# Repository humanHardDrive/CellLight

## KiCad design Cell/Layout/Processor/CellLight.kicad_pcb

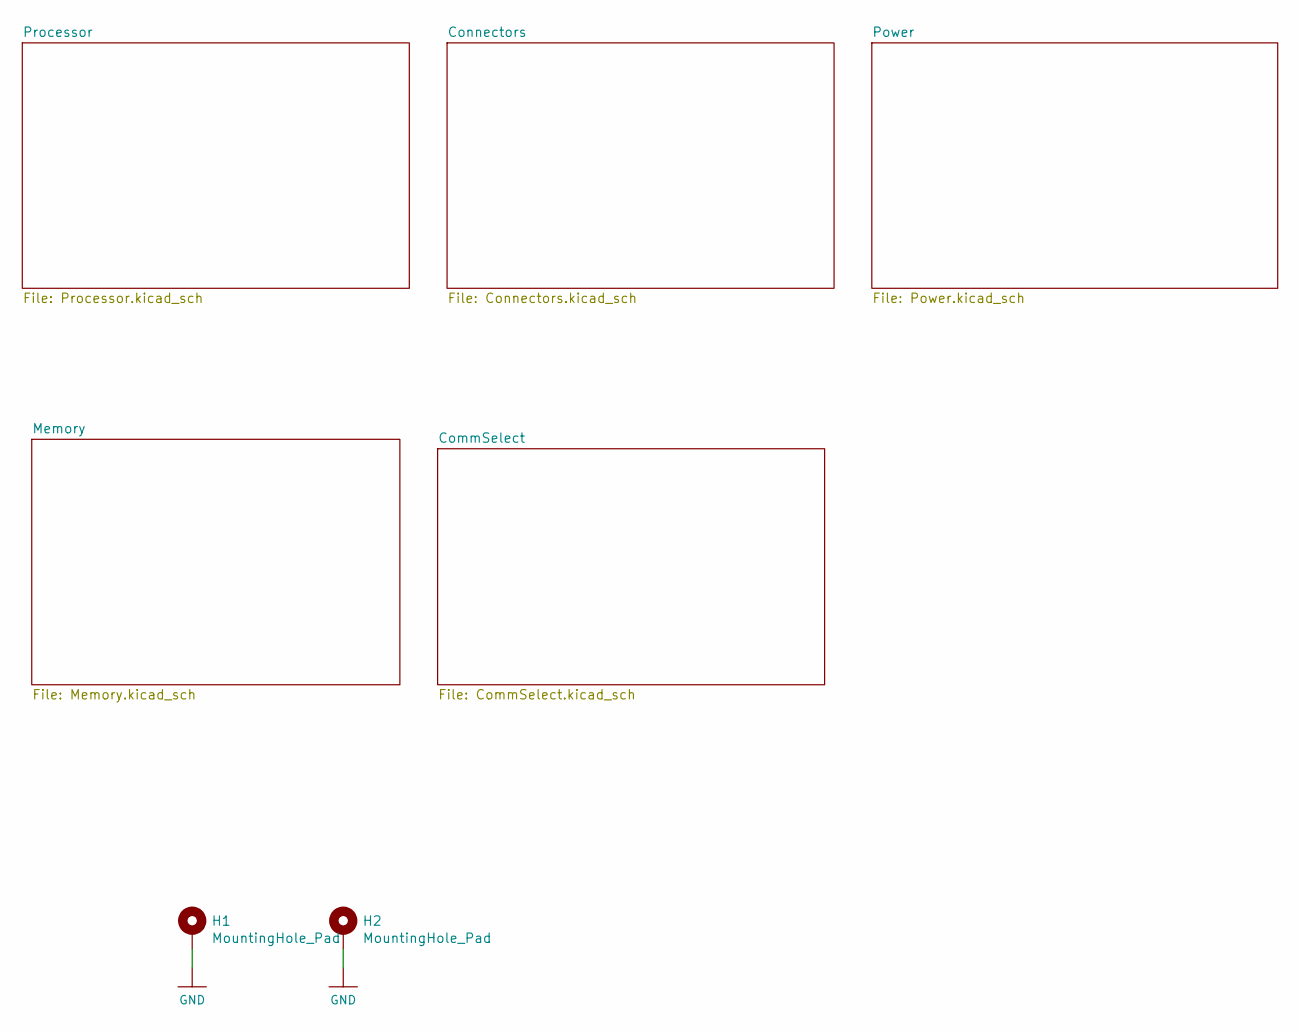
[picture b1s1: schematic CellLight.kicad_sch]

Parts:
H1, H2: MountingHole_Pad; MountingHole_2.7mm_M2.5_Pad

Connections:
GND: H1.1, H2.1; also elsewhere on the board

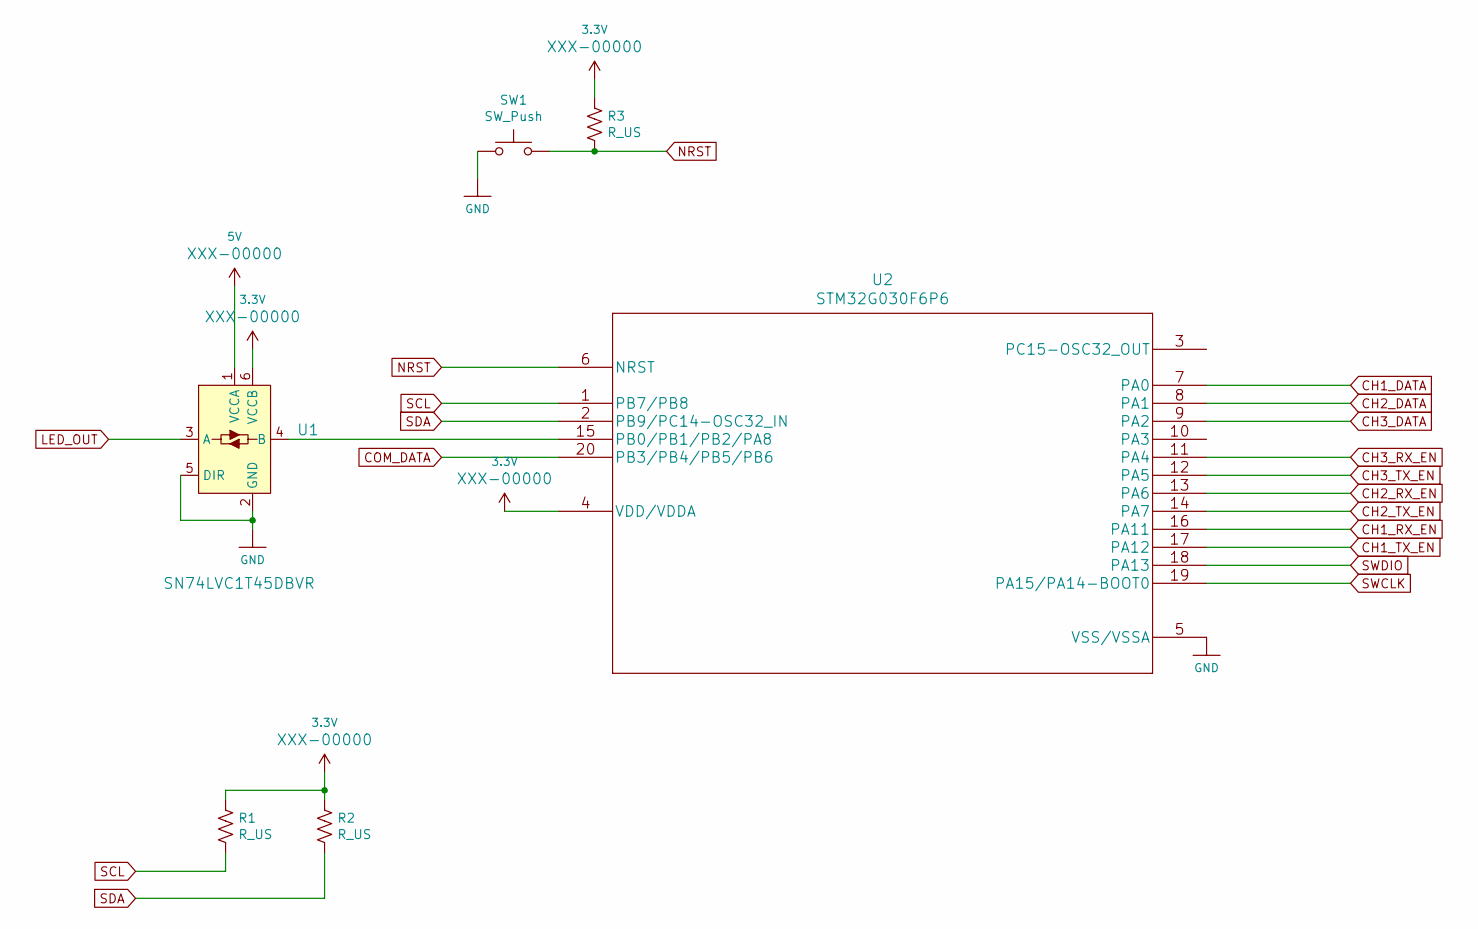
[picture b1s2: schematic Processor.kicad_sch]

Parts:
R1, R2, R3: R_US; R_0603_1608Metric_Pad1.05x0.95mm_HandSolder
SW1: SW_Push; SW_SPST_TL3342
U1: SN74LVC1T45DBVR; SOT-23-6; MPN SN74LVC1T45DBVR; Digi-Key_PN 296-16843-1-ND
U2: STM32G030F6P6

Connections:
3.3V: R1.1, R2.1, R3.1, U1.6 (VCCB), U2.4 (VDD/VDDA); also elsewhere on the board
5V: U1.1 (VCCA); also elsewhere on the board
CH1_DATA: U2.7 (PA0); also elsewhere on the board
CH1_RX_EN: U2.16 (PA11); also elsewhere on the board
CH1_TX_EN: U2.17 (PA12); also elsewhere on the board
CH2_DATA: U2.8 (PA1); also elsewhere on the board
CH2_RX_EN: U2.13 (PA6); also elsewhere on the board
CH2_TX_EN: U2.14 (PA7); also elsewhere on the board
CH3_DATA: U2.9 (PA2); also elsewhere on the board
CH3_RX_EN: U2.11 (PA4); also elsewhere on the board
CH3_TX_EN: U2.12 (PA5); also elsewhere on the board
COM_DATA: U2.20 (PB3/PB4/PB5/PB6); also elsewhere on the board
GND: SW1.1, U1.2 (GND), U1.5 (DIR), U2.5 (VSS/VSSA); also elsewhere on the board
LED_OUT: U1.3 (A); also elsewhere on the board
NRST: R3.2, SW1.2, U2.6 (NRST); also elsewhere on the board
unnamed: U1.4 (B), U2.15 (PB0/PB1/PB2/PA8)
SCL: R1.2, U2.1 (PB7/PB8); also elsewhere on the board
SDA: R2.2, U2.2 (PB9/PC14-OSC32_IN); also elsewhere on the board
SWCLK: U2.19 (PA15/PA14-BOOT0); also elsewhere on the board
SWDIO: U2.18 (PA13); also elsewhere on the board

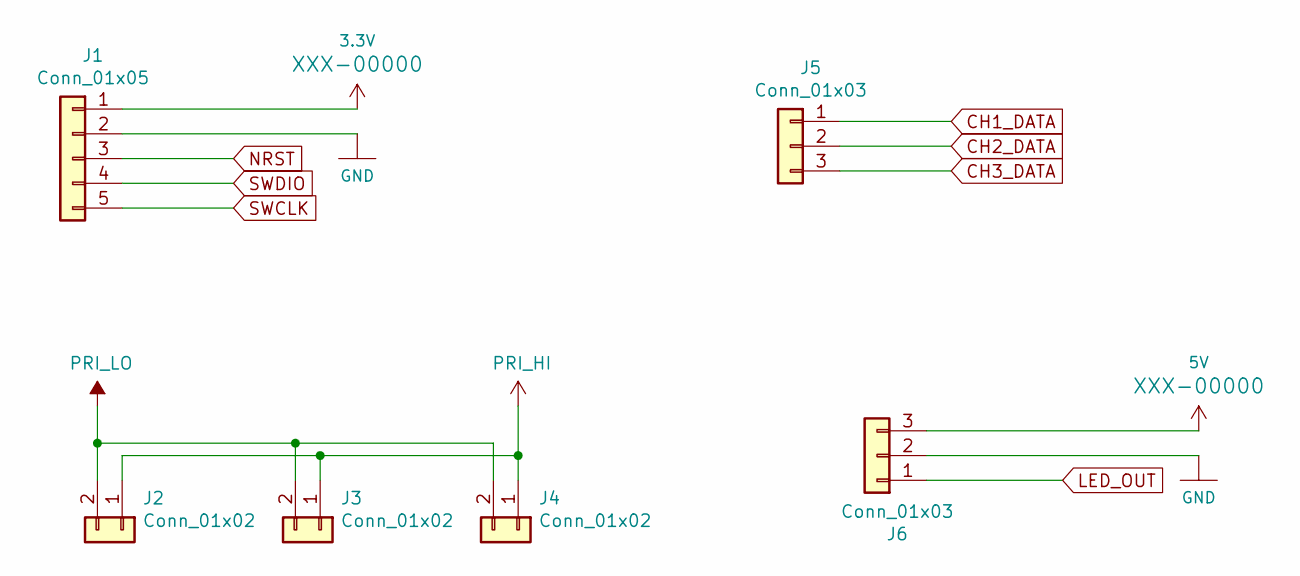
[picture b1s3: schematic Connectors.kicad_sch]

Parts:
J1: Conn_01x05; PinSocket_1x05_P2.54mm_Vertical
J2, J3, J4: Conn_01x02; JST_GH_BM02B-GHS-TBT_1x02-1MP_P1.25mm_Vertical
J5, J6: Conn_01x03; JST_GH_BM03B-GHS-TBT_1x03-1MP_P1.25mm_Vertical

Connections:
3.3V: J1.1; also elsewhere on the board
5V: J6.3; also elsewhere on the board
CH1_DATA: J5.1; also elsewhere on the board
CH2_DATA: J5.2; also elsewhere on the board
CH3_DATA: J5.3; also elsewhere on the board
GND: J1.2, J6.2; also elsewhere on the board
LED_OUT: J6.1; also elsewhere on the board
NRST: J1.3; also elsewhere on the board
PRI_HI: J2.1, J3.1, J4.1; also elsewhere on the board
PRI_LO: J2.2, J3.2, J4.2; also elsewhere on the board
SWCLK: J1.5; also elsewhere on the board
SWDIO: J1.4; also elsewhere on the board

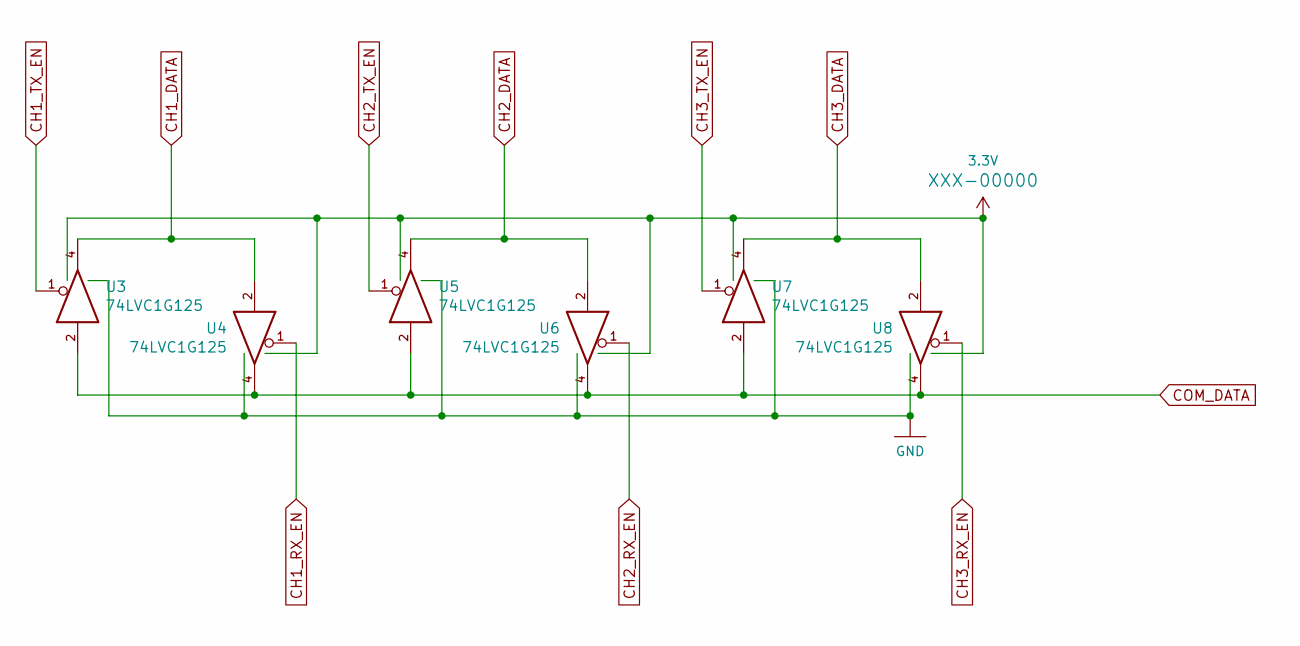
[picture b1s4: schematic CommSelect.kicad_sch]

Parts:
U3, U4, U5, U6, U7, U8: 74LVC1G125; SOT-353_SC-70-5_Handsoldering

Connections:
3.3V: U3.5 (VCC), U4.5 (VCC), U5.5 (VCC), U6.5 (VCC), U7.5 (VCC), U8.5 (VCC); also elsewhere on the board
CH1_DATA: U3.4, U4.2; also elsewhere on the board
CH1_RX_EN: U4.1; also elsewhere on the board
CH1_TX_EN: U3.1; also elsewhere on the board
CH2_DATA: U5.4, U6.2; also elsewhere on the board
CH2_RX_EN: U6.1; also elsewhere on the board
CH2_TX_EN: U5.1; also elsewhere on the board
CH3_DATA: U7.4, U8.2; also elsewhere on the board
CH3_RX_EN: U8.1; also elsewhere on the board
CH3_TX_EN: U7.1; also elsewhere on the board
COM_DATA: U3.2, U4.4, U5.2, U6.4, U7.2, U8.4; also elsewhere on the board
GND: U3.3 (GND), U4.3 (GND), U5.3 (GND), U6.3 (GND), U7.3 (GND), U8.3 (GND); also elsewhere on the board

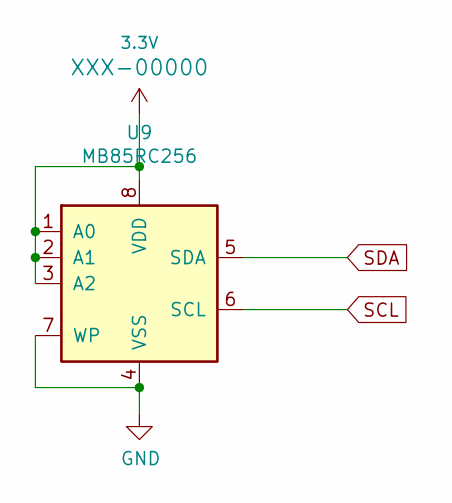
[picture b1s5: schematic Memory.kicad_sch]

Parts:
U9: MB85RC256; SOIC-8_3.9x4.9mm_P1.27mm

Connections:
3.3V: U9.1 (A0), U9.2 (A1), U9.3 (A2), U9.8 (VDD); also elsewhere on the board
GND: U9.4 (VSS), U9.7 (WP); also elsewhere on the board
SCL: U9.6 (SCL); also elsewhere on the board
SDA: U9.5 (SDA); also elsewhere on the board

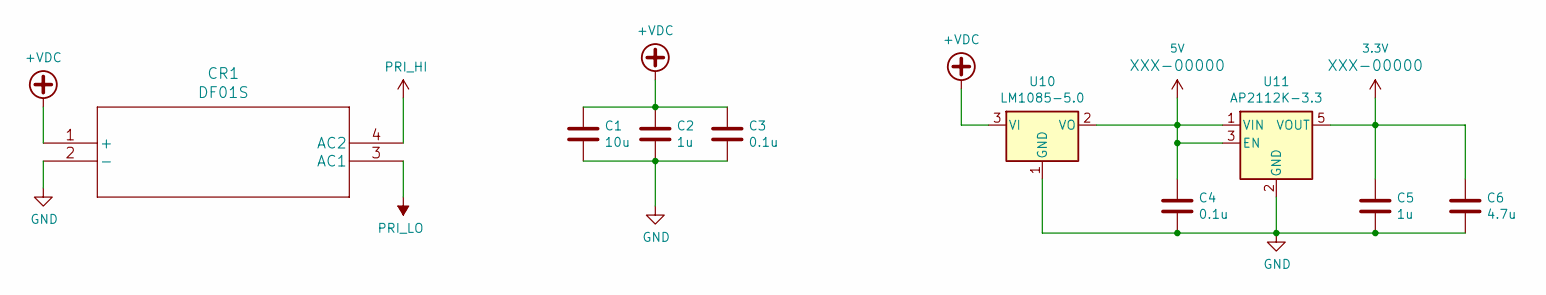
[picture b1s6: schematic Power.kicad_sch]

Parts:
C1: 10u; C_0603_1608Metric_Pad1.05x0.95mm_HandSolder
C2, C5: 1u; C_0603_1608Metric_Pad1.05x0.95mm_HandSolder
C3, C4: 0.1u; C_0603_1608Metric_Pad1.05x0.95mm_HandSolder
C6: 4.7u; C_0603_1608Metric_Pad1.05x0.95mm_HandSolder
CR1: DF01S
U10: LM1085-5.0; TO-263-3_TabPin2
U11: AP2112K-3.3; SOT-23-5

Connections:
3.3V: C5.1, C6.1, U11.5 (VOUT); also elsewhere on the board
5V: C4.1, U10.2 (VO), U11.1 (VIN), U11.3 (EN); also elsewhere on the board
+VDC: C1.1, C2.1, C3.1, CR1.1 (+), U10.3 (VI)
GND: C1.2, C2.2, C3.2, C4.2, C5.2, C6.2, CR1.2 (-), U10.1 (GND), U11.2 (GND); also elsewhere on the board
PRI_HI: CR1.4 (AC2); also elsewhere on the board
PRI_LO: CR1.3 (AC1); also elsewhere on the board

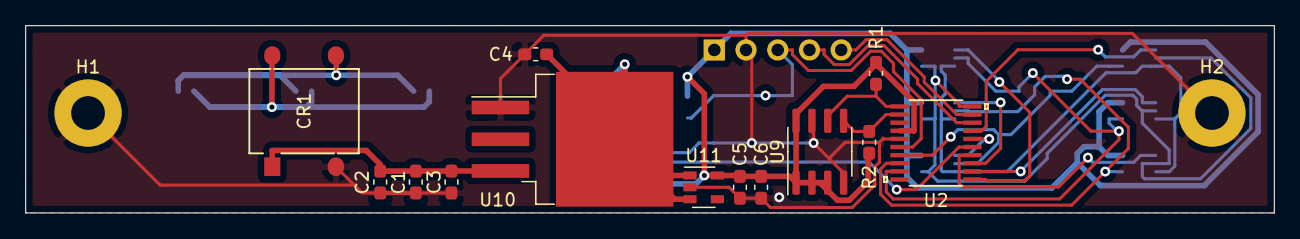
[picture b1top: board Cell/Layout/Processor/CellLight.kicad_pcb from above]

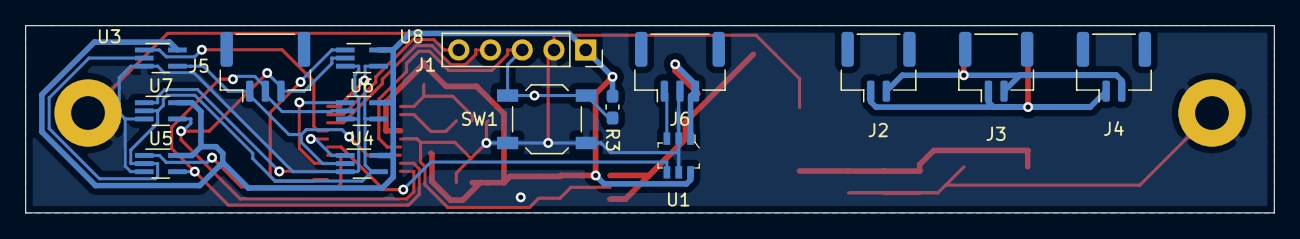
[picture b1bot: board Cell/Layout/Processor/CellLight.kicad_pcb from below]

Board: 2 copper layers, 100.0 x 15.0 mm, 30 parts (15 on the bottom side), 23 nets.

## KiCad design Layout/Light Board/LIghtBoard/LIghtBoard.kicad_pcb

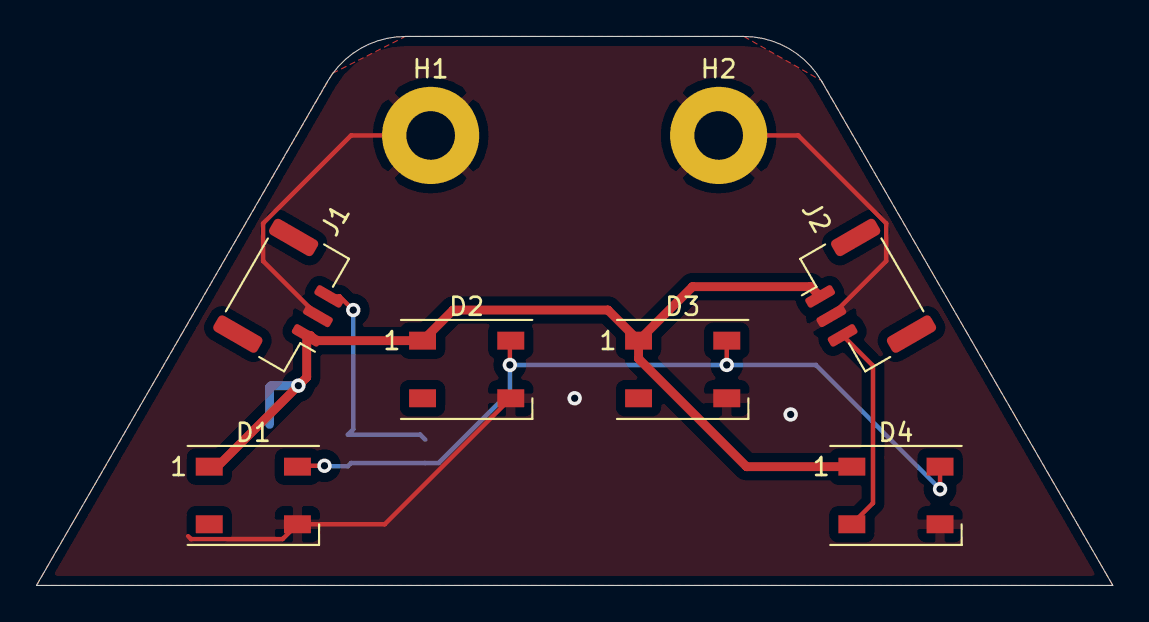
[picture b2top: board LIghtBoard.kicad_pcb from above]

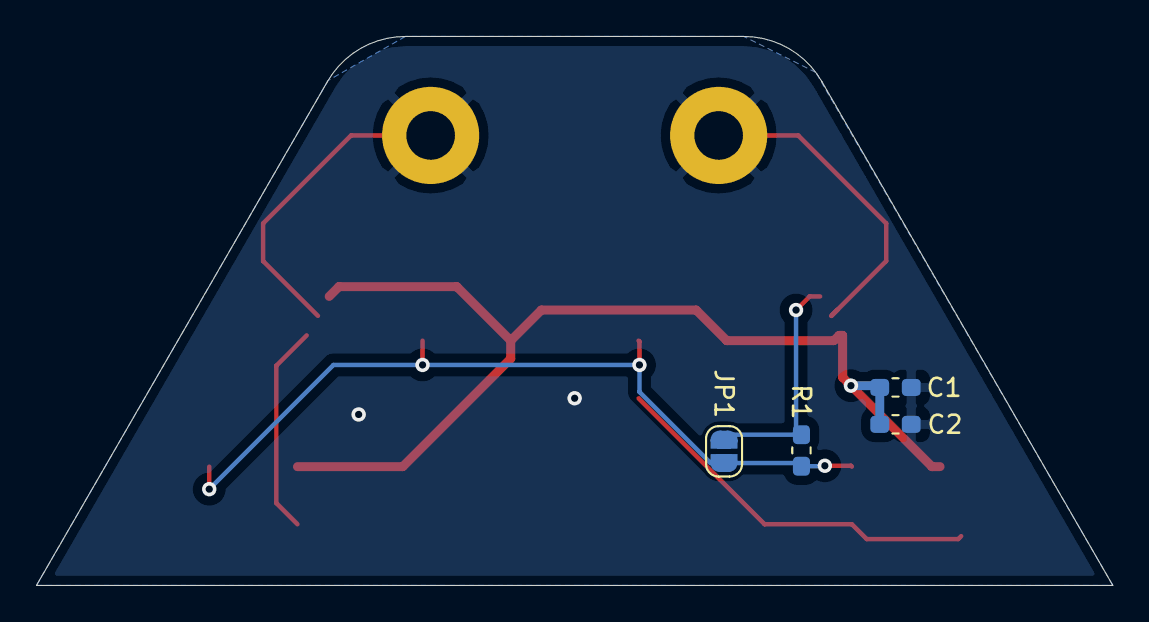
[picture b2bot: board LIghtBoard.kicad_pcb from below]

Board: 2 copper layers, 59.8 x 30.5 mm, 12 parts (4 on the bottom side), 5 nets.

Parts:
C1, C2: C; C_0603_1608Metric_Pad1.05x0.95mm_HandSolder
D1, D2, D3, D4: WS2812B; LED_WS2812B_PLCC4_5.0x5.0mm_P3.2mm
H1, H2: MountingHole_Pad; MountingHole_2.7mm_M2.5_Pad
J1, J2: Conn_01x03; JST_GH_BM03B-GHS-TBT_1x03-1MP_P1.25mm_Vertical
JP1: Jumper_2_Open; SolderJumper-2_P1.3mm_Open_RoundedPad1.0x1.5mm
R1: R_US; R_0603_1608Metric_Pad1.05x0.95mm_HandSolder

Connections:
5V: C1.1, C2.1, D1.1, D2.1, D3.1, D4.1, J1.1, J2.1
/Din: J1.3, JP1.2, R1.1
/Dout: D4.2, J2.3
GND: C1.2, C2.2, D1.3, D2.3, D3.3, D4.3, H1.1, H2.1, J1.2, J2.2
unnamed: D1.4, D2.4, D3.4, D4.4, JP1.1, R1.2

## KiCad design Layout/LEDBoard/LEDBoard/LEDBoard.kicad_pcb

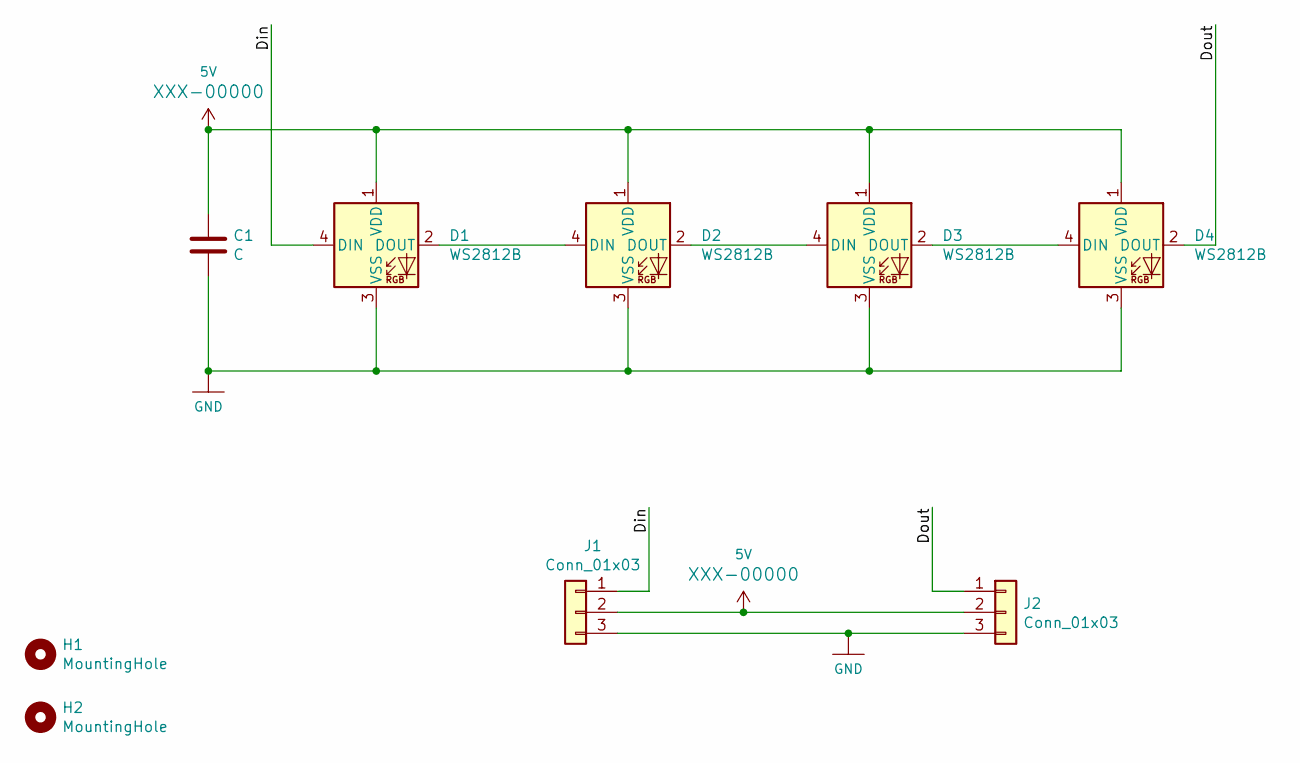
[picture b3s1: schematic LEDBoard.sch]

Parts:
C1: C; C_0603_1608Metric_Pad1.05x0.95mm_HandSolder
D1, D2, D3, D4: WS2812B; LED_WS2812B_PLCC4_5.0x5.0mm_P3.2mm
H1, H2: MountingHole; MountingHole_2.7mm_M2.5_Pad
J1, J2: Conn_01x03; JST_SUR_SM03B-SURS-TF_1x03-1MP_P0.80mm_Horizontal

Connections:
5V: C1.1, D1.1 (VDD), D2.1 (VDD), D3.1 (VDD), D4.1 (VDD), J1.2, J2.2
/Din: D1.4 (DIN), J1.1
/Dout: D4.2 (DOUT), J2.1
GND: C1.2, D1.3 (VSS), D2.3 (VSS), D3.3 (VSS), D4.3 (VSS), J1.3, J2.3
unnamed: D1.2 (DOUT), D2.4 (DIN)
unnamed: D2.2 (DOUT), D3.4 (DIN)
unnamed: D3.2 (DOUT), D4.4 (DIN)

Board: 2 copper layers, 9 parts (1 on the bottom side), 7 nets, no tracks yet.

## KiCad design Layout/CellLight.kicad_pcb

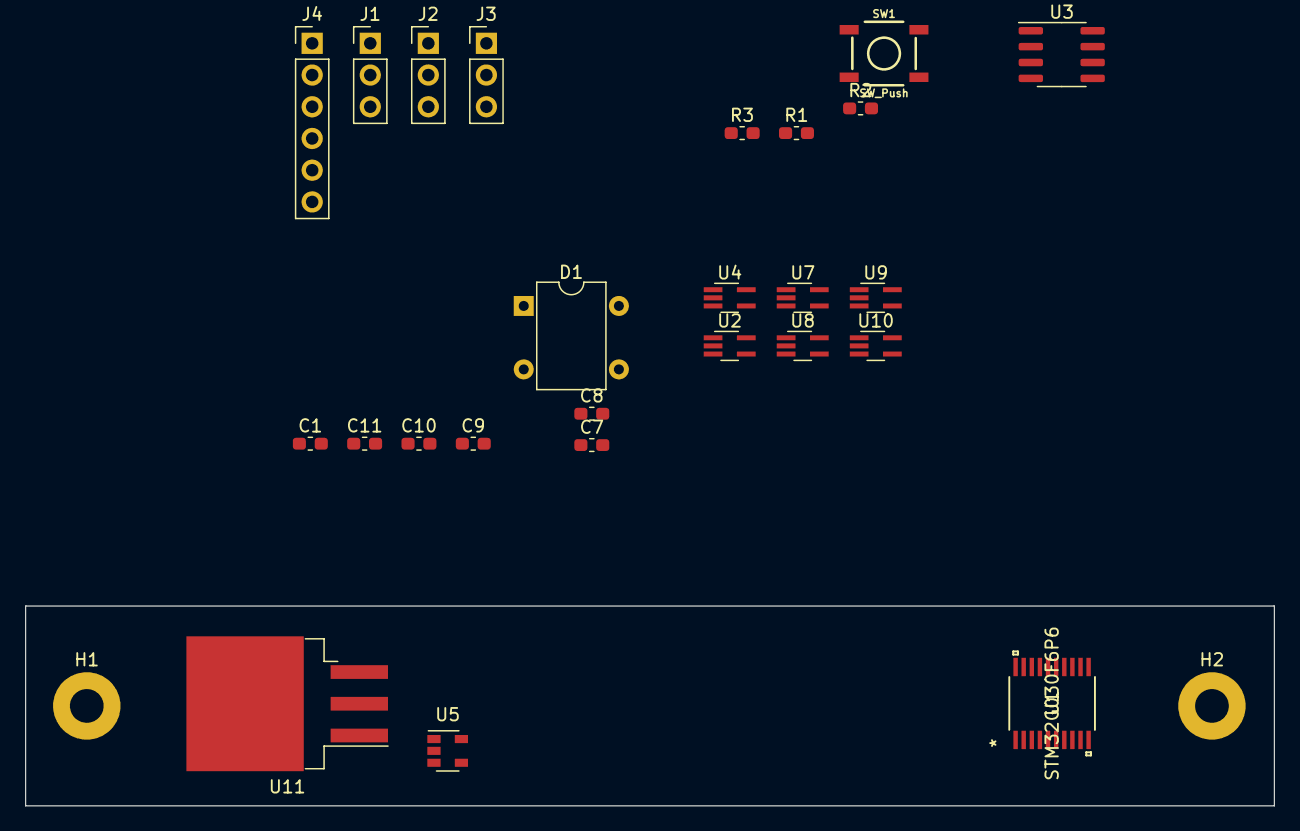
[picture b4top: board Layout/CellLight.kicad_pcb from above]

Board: 2 copper layers, 100.0 x 16.0 mm, 27 parts (0 on the bottom side), 20 nets, no tracks yet.

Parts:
C1: 4.7u; C_0603_1608Metric_Pad1.05x0.95mm_HandSolder
C7: 10u; C_0603_1608Metric_Pad1.05x0.95mm_HandSolder
C8, C11: 1u; C_0603_1608Metric_Pad1.05x0.95mm_HandSolder
C9, C10: 0.1u; C_0603_1608Metric_Pad1.05x0.95mm_HandSolder
D1: DF02M; Diode_Bridge_DIP-4_W7.62mm_P5.08mm
H1, H2: MountingHole; MountingHole_2.7mm_M2.5_Pad
J1, J2, J3: Conn_01x03; PinHeader_1x03_P2.54mm_Vertical
J4: Conn_01x06; PinHeader_1x06_P2.54mm_Vertical
R1, R2, R3: R_US; R_0603_1608Metric_Pad1.05x0.95mm_HandSolder
SW1: SW_Push; TACTILE_SWITCH_SMD_5.2MM
U1: STM32G030F6P6
U2, U4, U7, U8, U9, U10: 74LVC1G125; SOT-353_SC-70-5_Handsoldering
U3: MB85RC256; SOIC-8_3.9x4.9mm_P1.27mm
U5: AP2112K-3.3; SOT-23-5
U11: LM1085-5.0; TO-263-3_TabPin2

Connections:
3.3V: R1.1, R2.1, R3.1, U1.4, U2.5, U4.5, U7.5, U8.5, U9.5, U10.5
+3V3: C1.1, C11.1, J4.2, U3.1, U3.2, U3.3, U3.8, U5.5
+5V: C10.1, U5.1, U5.3, U11.2
+VDC: C7.1, C8.1, C9.1, D1.1, U11.3
/Processor/RESET: R1.2, SW1.2, U1.6
CH1_DATA: U1.7, U2.4, U4.2
CH1_RX_EN: U1.16, U4.1
CH1_TX_EN: U1.17, U2.1
CH2_DATA: U1.8, U7.4, U8.2
CH2_RX_EN: U1.13, U8.1
CH2_TX_EN: U1.14, U7.1
CH3_DATA: U1.9, U9.4, U10.2
CH3_RX_EN: U1.11, U10.1
CH3_TX_EN: U1.12, U9.1
COM_DATA: U1.20, U2.2, U4.4, U7.2, U8.4, U9.2, U10.4
GND: C1.2, C7.2, C8.2, C9.2, C10.2, C11.2, D1.2, J4.3, SW1.1, U1.5, U2.3, U3.4, U4.3, U5.2, U7.3, U8.3, U9.3, U10.3, U11.1
PRI_HI: D1.4, J1.1, J2.1, J3.1
PRI_LO: D1.3, J1.2, J2.2, J3.2
SCL: R2.2, U1.1, U3.6
SDA: R3.2, U1.2, U3.5

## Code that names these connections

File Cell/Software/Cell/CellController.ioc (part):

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Mcu.Name=STM32G030F6Px
Mcu.Package=TSSOP20
Mcu.UserName=STM32G030F6Px
PA0.GPIOParameters=GPIO_Label
PA0.GPIO_Label=CH1DataDetect
PA0.Signal=GPIO_Input
PA1.GPIOParameters=GPIO_Label
PA1.GPIO_Label=CH2DataDetect
PA1.Signal=GPIO_Input
PA11\ [PA9].GPIOParameters=GPIO_Label
PA11\ [PA9].GPIO_Label=CH1RXEnable
PA11\ [PA9].Signal=GPIO_Output
PA12\ [PA10].GPIOParameters=GPIO_Label
PA12\ [PA10].GPIO_Label=CH1TXEnable
PA12\ [PA10].Signal=GPIO_Output
PA14-BOOT0__PA15.StandardMode=true
PA2.GPIOParameters=GPIO_Label
PA2.GPIO_Label=CH3DataDetect
PA2.Signal=GPIO_Input
PA4.GPIOParameters=GPIO_Label
PA4.GPIO_Label=CH3RXEnable
PA4.Signal=GPIO_Output
PA5.GPIOParameters=GPIO_Label
PA5.GPIO_Label=CH3TXEnable
PA5.Signal=GPIO_Output
PA6.GPIOParameters=GPIO_Label
PA6.GPIO_Label=CH2RXEnable
PA6.Signal=GPIO_Output
PA7.GPIOParameters=GPIO_Label
PA7.GPIO_Label=CH2TXEnable
PA7.Signal=GPIO_Output
PB0.Signal=S_TIM3_CH3
PB0__PB1__PB2__PA8.StandardMode=true
PB3__PB4__PB5__PB6.StandardMode=true
PB6.Mode=Half_duplex(single_wire_mode)
PB6.Signal=USART1_TX
PB7__PB8.StandardMode=true
PB8.Mode=I2C
PB8.Signal=I2C1_SCL
PB9.Mode=I2C
PB9.Signal=I2C1_SDA
PC14-OSC32_IN\ (PC14)__PB9.StandardMode=true
RCC.HSE_VALUE=8000000
RCC.SYSCLKFreq_VALUE=16000000
board=custom

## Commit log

2019-04-22 Add project files
2019-04-22 Add source files
2019-04-23 Add stub functions
2019-04-23 Setup some debug port stuff
2019-05-12 Setup clock switching to external crystal
2019-05-12 Configure degug port
2019-05-12 Setup the TX/RX buffers. Move the debug port onto the 5v toolerant pins
2019-05-12 Create a print string method
2019-05-12 Setup cursor commands for teraterm
2019-05-12 Setup basic menu control
2019-05-12 Setup intra-cell UART ports
2019-05-13 Setup the color control timer and DMA
    Add the interrupt handlers for the communication router and some message definitions.
2019-05-13 Add color control to debug menu.
    Change color control DMA to use a repeated one-shot to prevent the channel from being disabled.
2019-05-14 Setup comm router parsing
2019-05-15 Change color from debug menu. Fix color generation.
2019-05-15 Setup comm router uart buffers
2019-05-15 Create memcopy for cyclical buffer
2019-05-15 Create color cycle test
2019-05-16 Start message routing
2019-05-16 Modify color cycle
2019-05-16 Add some macros. Need to re-write the comm router to be per port. May simplify code.
2019-05-17 Create port specific write functions that are selected via array.
2019-05-17 Flush out port specific write methods
2019-12-16 Add schematic
2020-08-12 Clear out repository
2020-08-13 Add new schematic
2020-08-13 Add more sheets. Add LEDs
2020-08-14 Add voltage regulators
2020-08-14 Add programming header
2020-08-14 Add memory
2020-08-14 Add footprints
2020-08-14 Add logic translator for LED
2020-08-14 Update footprints and references
2020-08-14 Add MPLab project
2020-08-15 Generate PCB layout
2020-08-15 Create schematic PDF and gerber files
2020-08-15 Add some code
2020-08-26 Create LICENSE
2020-09-09 Change processor to something with a different package
2020-09-09 Fix connector footprint
2020-09-10 Remap IO
2020-09-10 Priliminary PCB layout
2020-09-11 Route the PCB
2020-09-29 Layout
2020-11-05 Update schematic for new processor
2020-11-08 Adjust layouts
2020-11-08 Move files around
2020-11-08 Add controller project
2020-11-09 Do the processor board layout
2020-11-11 Finish layouts
2020-11-11 Remove old code
2020-11-11 Add new code project
2020-11-21 Add controller software files
2020-11-22 Add new files for WebUI
2020-11-22 Add control.js
2020-11-22 Add basic html
2020-11-26 Add controls to layout cells
2020-11-27 Setup some schematics
2020-11-27 Fix adding shared cells
2023-07-09 Remove the old controller
    Remove the linux based controller and switch to an ESP8266 based controller.
2023-07-17 Add debug
2023-07-18 Add color blending reference code
2023-07-18 Remove cell controller project
2023-08-20 Remove old cell controller project. Add new project. Ignore the right files

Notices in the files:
parts and their libraries:
Copyright 2016 Accelerated Designs. All rights reserved.
